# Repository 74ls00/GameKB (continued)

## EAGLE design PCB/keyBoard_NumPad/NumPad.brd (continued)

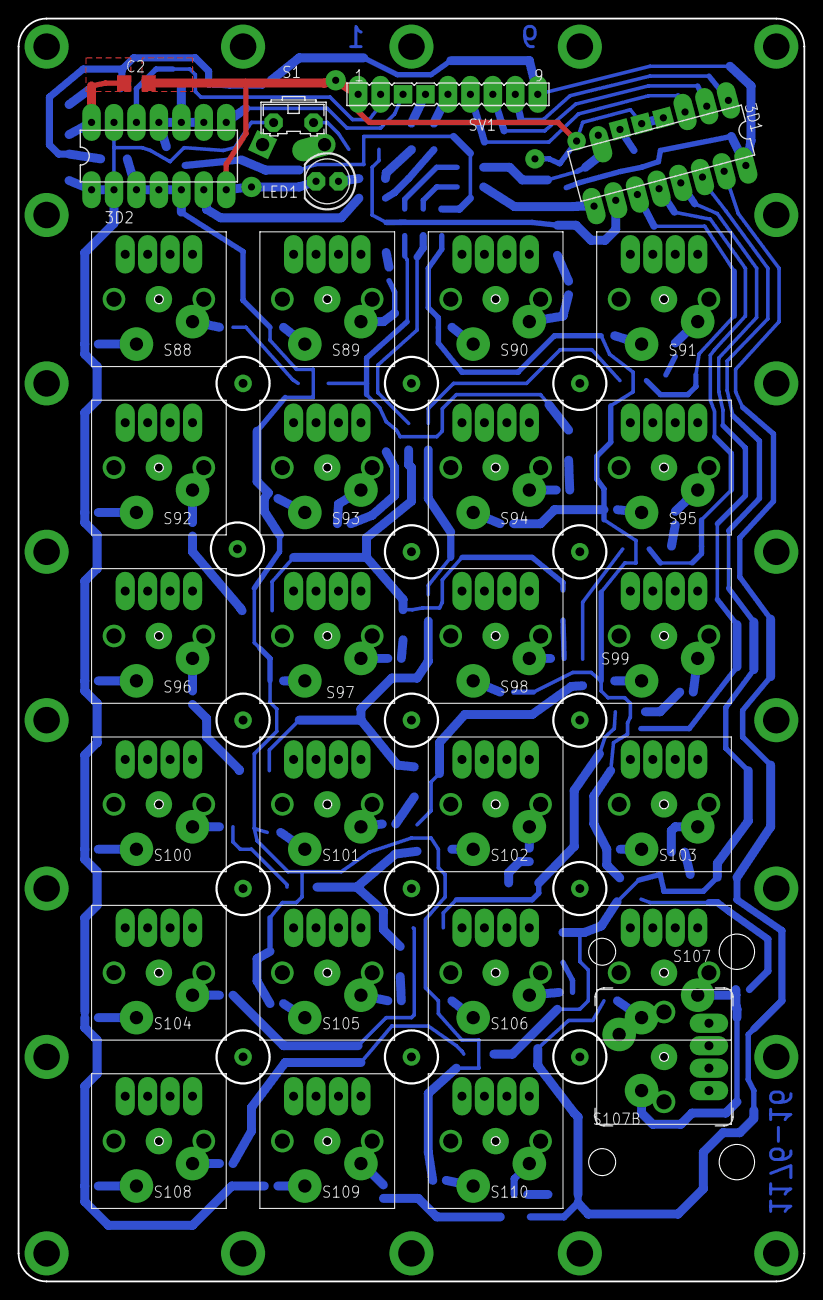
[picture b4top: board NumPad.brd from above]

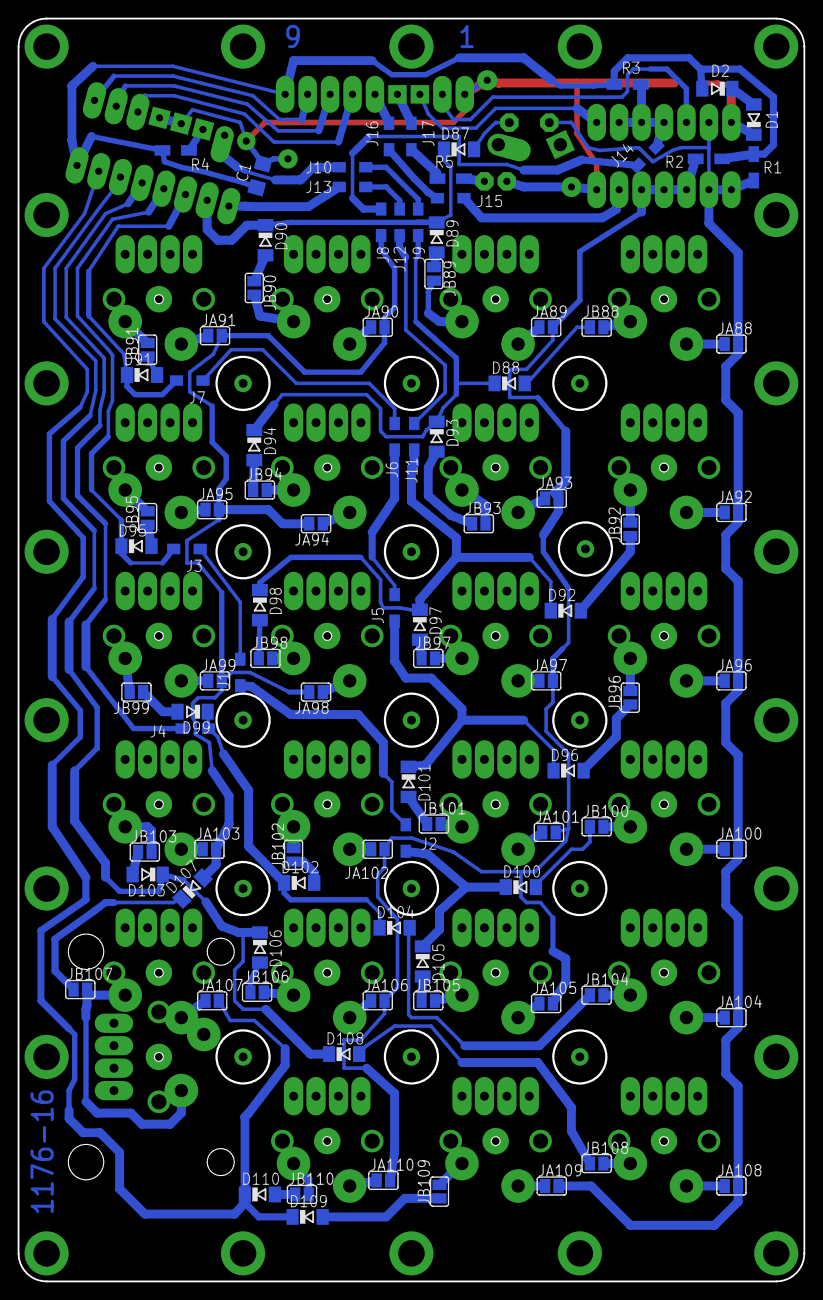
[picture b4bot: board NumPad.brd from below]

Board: 2 copper layers, 88.9 x 142.9 mm, 175 parts (23 on the bottom side), 111 nets.

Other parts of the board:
U$1, U$88, U$89, U$90, U$91, U$92, U$93, U$94, U$95, U$96, U$97, U$98, U$99, U$100, U$101, U$102, U$103, U$104, U$105, U$106, U$107, U$108, U$109, U$110: 18X18
U$2: NUMENTER
U$3, U$4, U$5, U$6, U$7, U$8, U$9, U$10, U$11, U$12, U$13, U$14, U$15, U$16, U$17, U$18, U$19, U$20, U$21, U$22, U$23, U$24: KEY
U$26: SIZE132
U$111: 37X18

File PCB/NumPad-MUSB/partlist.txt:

Partlist

Exported from NumPad.sch at 11.08.2016 8:09:16

EAGLE Version 6.3.0 Copyright (c) 1988-2012 CadSoft

Assembly variant: 

Part     Value          Device       Package      Library  Sheet

3D1      74HC138N       74HC138N     DIL16        detali   1
3D2      Ê155ÈÄ4        74HC10N      DIL14        detali   1
C1                      C-EUC1206    C1206        rcl      1
C2                      C-EUC1206    C1206        rcl      1
D1       LL4148         LL4148       SOD80C       detali   1
D2       LL4148         LL4148       SOD80C       detali   1
D87      LL4148         LL4148       SOD80C       detali   1
D88      LL4148         LL4148       SOD80C       detali   1
D89      LL4148         LL4148       SOD80C       detali   1
D90      LL4148         LL4148       SOD80C       detali   1
D91      LL4148         LL4148       SOD80C       detali   1
D92      LL4148         LL4148       SOD80C       detali   1
D93      LL4148         LL4148       SOD80C       detali   1
D94      LL4148         LL4148       SOD80C       detali   1
D95      LL4148         LL4148       SOD80C       detali   1
D96      LL4148         LL4148       SOD80C       detali   1
D97      LL4148         LL4148       SOD80C       detali   1
D98      LL4148         LL4148       SOD80C       detali   1
D99      LL4148         LL4148       SOD80C       detali   1
D100     LL4148         LL4148       SOD80C       detali   1
D101     LL4148         LL4148       SOD80C       detali   1
D102     LL4148         LL4148       SOD80C       detali   1
D103     LL4148         LL4148       SOD80C       detali   1
D104     LL4148         LL4148       SOD80C       detali   1
D105     LL4148         LL4148       SOD80C       detali   1
D106     LL4148         LL4148       SOD80C       detali   1
D107     LL4148         LL4148       SOD80C       detali   1
D108     LL4148         LL4148       SOD80C       detali   1
D109     LL4148         LL4148       SOD80C       detali   1
D110     LL4148         LL4148       SOD80C       detali   1
J1       J              J            R1206W       detali   1
J2       J              J            R1206W       detali   1
J3       J              J            R1206W       detali   1
J4       J              J            R1206W       detali   1
J5       J              J            R1206W       detali   1
J6       J              J            R1206W       detali   1
J7       J              J            R1206W       detali   1
J8       J              J            R1206W       detali   1
J9       J              J            R1206W       detali   1
J10      J              J            R1206W       detali   1
J11      J              J            R1206W       detali   1
J12      J              J            R1206W       detali   1
J13      J              J            R1206W       detali   1
J14      J              J            R1206W       detali   1
J15      J              J            R1206W       detali   1
J16      J              J            R1206W       detali   1
J17      J              J            R1206W       detali   1
JA88                    SJ           SJ           detali   1
JA89                    SJ           SJ           detali   1
JA90                    SJ           SJ           detali   1
JA91                    SJ           SJ           detali   1
JA92                    SJ           SJ           detali   1
JA93                    SJ           SJ           detali   1
JA94                    SJ           SJ           detali   1
JA95                    SJ           SJ           detali   1
JA96                    SJ           SJ           detali   1
JA97                    SJ           SJ           detali   1
JA98                    SJ           SJ           detali   1
JA99                    SJ           SJ           detali   1
JA100                   SJ           SJ           detali   1
JA101                   SJ           SJ           detali   1
JA102                   SJ           SJ           detali   1
JA103                   SJ           SJ           detali   1
JA104                   SJ           SJ           detali   1
JA105                   SJ           SJ           detali   1
JA106                   SJ           SJ           detali   1
JA107                   SJ           SJ           detali   1
JA108                   SJ           SJ           detali   1
JA109                   SJ           SJ           detali   1
JA110                   SJ           SJ           detali   1
JB88                    SJ           SJ           detali   1
JB89                    SJ           SJ           detali   1
JB90                    SJ           SJ           detali   1
JB91                    SJ           SJ           detali   1
JB92                    SJ           SJ           detali   1
JB93                    SJ           SJ           detali   1
JB94                    SJ           SJ           detali   1
JB95                    SJ           SJ           detali   1
JB96                    SJ           SJ           detali   1
JB97                    SJ           SJ           detali   1
JB98                    SJ           SJ           detali   1
JB99                    SJ           SJ           detali   1
JB100                   SJ           SJ           detali   1
JB101                   SJ           SJ           detali   1
JB102                   SJ           SJ           detali   1
JB103                   SJ           SJ           detali   1
JB104                   SJ           SJ           detali   1
JB105                   SJ           SJ           detali   1
JB106                   SJ           SJ           detali   1
JB107                   SJ           SJ           detali   1
JB108                   SJ           SJ           detali   1
JB109                   SJ           SJ           detali   1
JB110                   SJ           SJ           detali   1
LED1                    LED5MM       LED5MM       detali   1
R1       10k            R-EU_R1206W  R1206W       rcl      1
R2       10k            R-EU_R1206W  R1206W       rcl      1
R3       10k            R-EU_R1206W  R1206W       rcl      1
R4                      R-EU_R1206W  R1206W       rcl      1
R5                      R-EU_R1206W  R1206W       rcl      1
S1       NumLock        31-XX        B3F-31XX     detali   1
S88      D              CHERRY-MX-4P CHERRY-MX-4P cherrymx 1
S89      E              CHERRY-MX-4P CHERRY-MX-4P cherrymx 1
S90      F              CHERRY-MX-4P CHERRY-MX-4P cherrymx 1
S91      /              CHERRY-MX-4P CHERRY-MX-4P cherrymx 1
S92      A              CHERRY-MX-4P CHERRY-MX-4P cherrymx 1
S93      B              CHERRY-MX-4P CHERRY-MX-4P cherrymx 1
S94      C              CHERRY-MX-4P CHERRY-MX-4P cherrymx 1
S95      *              CHERRY-MX-4P CHERRY-MX-4P cherrymx 1
S96      7              CHERRY-MX-4P CHERRY-MX-4P cherrymx 1
S97      8              CHERRY-MX-4P CHERRY-MX-4P cherrymx 1
S98      9              CHERRY-MX-4P CHERRY-MX-4P cherrymx 1
S99      -              CHERRY-MX-4P CHERRY-MX-4P cherrymx 1
S100     4              CHERRY-MX-4P CHERRY-MX-4P cherrymx 1
S101     5              CHERRY-MX-4P CHERRY-MX-4P cherrymx 1
S102     6              CHERRY-MX-4P CHERRY-MX-4P cherrymx 1
S103     +              CHERRY-MX-4P CHERRY-MX-4P cherrymx 1
S104     1              CHERRY-MX-4P CHERRY-MX-4P cherrymx 1
S105     2              CHERRY-MX-4P CHERRY-MX-4P cherrymx 1
S106     3              CHERRY-MX-4P CHERRY-MX-4P cherrymx 1
S107     NumEnter       CHERRY-MX-4P CHERRY-MX-4P cherrymx 1
S107B    NumEnter       CHERRY-MX-4P CHERRY-MX-4P cherrymx 1
S108     0              CHERRY-MX-4P CHERRY-MX-4P cherrymx 1
S109     00             CHERRY-MX-4P CHERRY-MX-4P cherrymx 1
S110     .              CHERRY-MX-4P CHERRY-MX-4P cherrymx 1
SV1                     FE09-1       FE09         detali   1

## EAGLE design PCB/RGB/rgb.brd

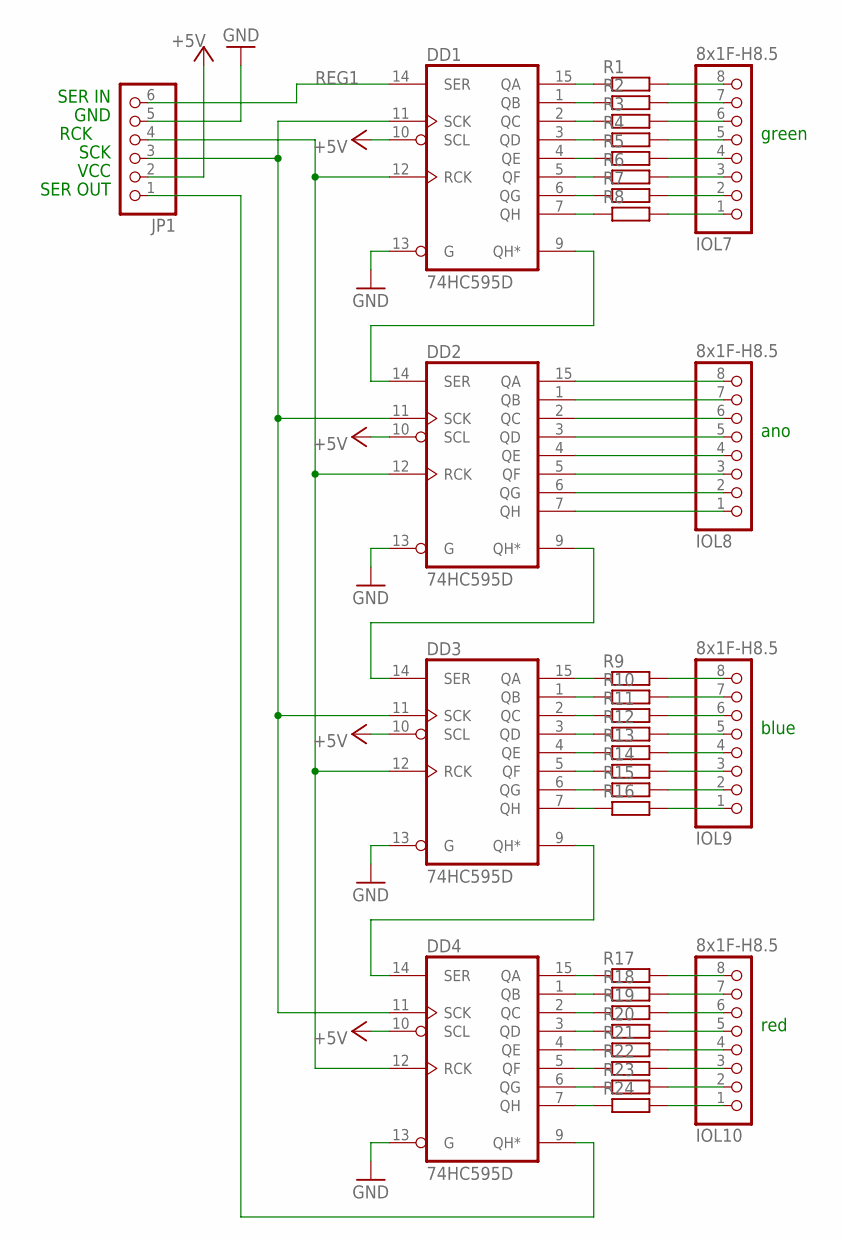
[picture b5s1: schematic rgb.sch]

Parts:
DD1, DD2, DD3, DD4: 74HC595D; SO16
IOL7, IOL8, IOL9, IOL10: 8x1F-H8.5; 1X08
JP1: PINHD-1X6; 1X06
R1, R2, R3, R4, R5, R6, R7, R8, R9, R10, R11, R12, R13, R14, R15, R16, R17, R18, R19, R20, R21, R22, R23, R24: R-EU_R0805; R0805

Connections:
+5V: DD1.10 (SCL), DD2.10 (SCL), DD3.10 (SCL), DD4.10 (SCL), JP1.2
GND: DD1.8 (GND), DD1.13 (G), DD2.8 (GND), DD2.13 (G), DD3.8 (GND), DD3.13 (G), DD4.8 (GND), DD4.13 (G), JP1.5
unnamed: DD1.15 (QA), R1.1
unnamed: DD1.1 (QB), R2.1
unnamed: DD1.2 (QC), R3.1
unnamed: DD1.3 (QD), R4.1
unnamed: DD1.4 (QE), R5.1
unnamed: DD1.5 (QF), R6.1
unnamed: DD1.6 (QG), R7.1
unnamed: DD1.7 (QH), R8.1
unnamed: DD3.15 (QA), R9.1
unnamed: DD3.1 (QB), R10.1
unnamed: DD3.2 (QC), R11.1
unnamed: DD3.3 (QD), R12.1
unnamed: DD3.4 (QE), R13.1
unnamed: DD3.5 (QF), R14.1
unnamed: DD3.6 (QG), R15.1
unnamed: DD3.7 (QH), R16.1
unnamed: DD4.15 (QA), R17.1
unnamed: DD4.1 (QB), R18.1
unnamed: DD4.2 (QC), R19.1
unnamed: DD4.3 (QD), R20.1
unnamed: DD4.4 (QE), R21.1
unnamed: DD4.5 (QF), R22.1
unnamed: DD4.6 (QG), R23.1
unnamed: DD4.7 (QH), R24.1
unnamed: IOL7.8, R1.2
unnamed: IOL7.7, R2.2
unnamed: DD2.15 (QA), IOL8.8
unnamed: DD2.1 (QB), IOL8.7
unnamed: DD2.2 (QC), IOL8.6
unnamed: DD1.9 (QH*), DD2.14 (SER)
unnamed: DD2.3 (QD), IOL8.5
unnamed: DD2.4 (QE), IOL8.4
unnamed: DD2.5 (QF), IOL8.3
unnamed: DD2.6 (QG), IOL8.2
unnamed: DD2.7 (QH), IOL8.1
unnamed: IOL7.6, R3.2
unnamed: IOL7.5, R4.2
unnamed: IOL7.4, R5.2
unnamed: IOL7.3, R6.2
unnamed: IOL7.2, R7.2
unnamed: IOL7.1, R8.2
unnamed: IOL9.8, R9.2
unnamed: IOL9.7, R10.2
unnamed: IOL9.6, R11.2
unnamed: IOL9.5, R12.2
unnamed: IOL9.4, R13.2
unnamed: IOL9.3, R14.2
unnamed: IOL9.2, R15.2
unnamed: IOL9.1, R16.2
unnamed: IOL10.8, R17.2
unnamed: IOL10.7, R18.2
unnamed: IOL10.6, R19.2
unnamed: IOL10.5, R20.2
unnamed: IOL10.4, R21.2
unnamed: IOL10.3, R22.2
unnamed: IOL10.2, R23.2
unnamed: IOL10.1, R24.2
unnamed: DD4.9 (QH*), JP1.1
unnamed: DD1.11 (SCK), DD2.11 (SCK), DD3.11 (SCK), DD4.11 (SCK), JP1.3
unnamed: DD1.12 (RCK), DD2.12 (RCK), DD3.12 (RCK), DD4.12 (RCK), JP1.4
unnamed: DD2.9 (QH*), DD3.14 (SER)
unnamed: DD3.9 (QH*), DD4.14 (SER)
REG1: DD1.14 (SER), JP1.6
VCC: DD1.16 (VCC), DD2.16 (VCC), DD3.16 (VCC), DD4.16 (VCC)

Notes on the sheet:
green
ano
blue
red
SER IN
SER OUT
GND
VCC
SCK
RCK

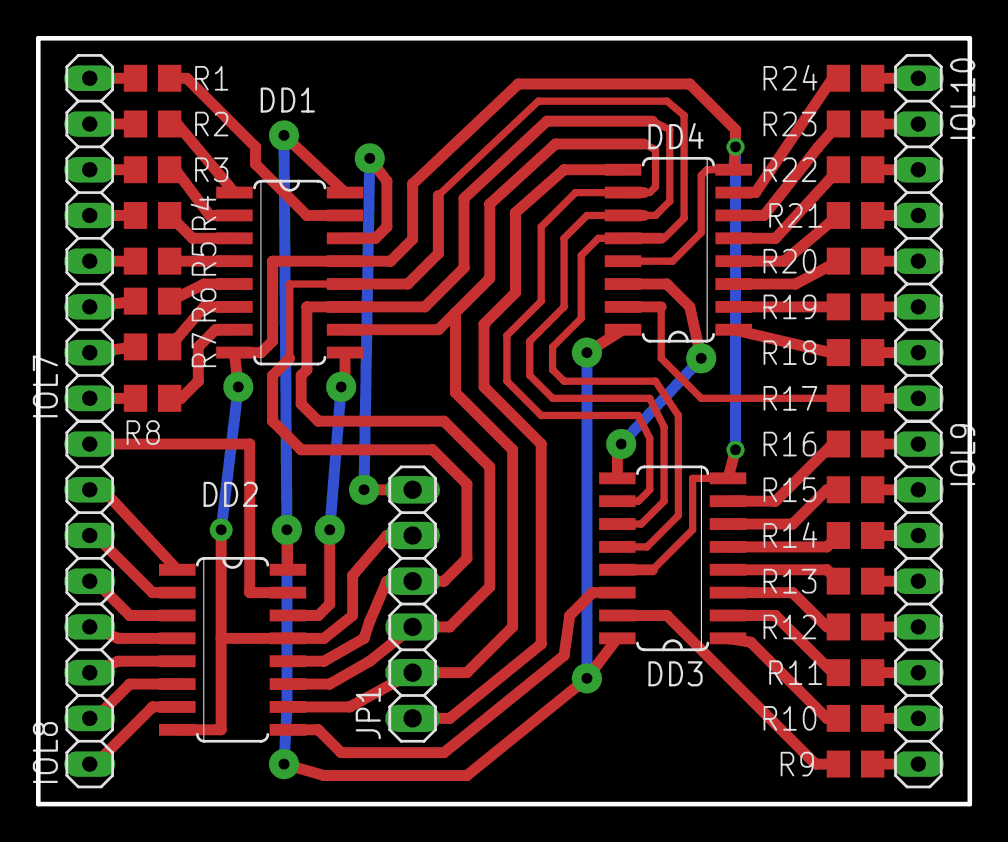
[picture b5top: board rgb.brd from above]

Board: 2 copper layers, 51.8 x 42.5 mm, 33 parts (0 on the bottom side), 66 nets.

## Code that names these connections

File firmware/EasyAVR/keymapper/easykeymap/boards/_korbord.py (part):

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#  |   avr           |      out_logic
#  |    |  port_avr  |         |   port_fw
#  |    |    |       |         |      |
# A0 = 36 = PD2 - 3,4,5   != 3D2_6  = 16 kbn3
# A1 = 37 = PD3 - 9,10,11 != 3D2_8  = 15 kbn2
# A2 = 38 = PD1 - 1,2,13  != 3D2_12 = 14 kbn1
# A4   40                             12 kbb1 
# D6   27                             10 kbb2
# D5   31   PC6                        1 kbb3
# D4   25   PD4                        7 kbb4    (x,7)
# A5   41                             11 kbb5
# D2   19   PD1                        4 kbb6
# D3(18) D7(1)  ? не нашёлся                                    
#
# D3    18  PD0                        3 kba2
# D0    20  PD2                        5 kba3
# D1    21  PD3                        6 kba4
# TxLED 22  PD5                        8 kba5
# D12   26  PD6                        9 kba6
# A3    39  PF4                       13 kba1

# keyBoard A (PCB_A) 
# порт в коде               0      4      2      6      1      5     3     7
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
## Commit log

2016-07-22 add led.c
2016-07-23 pcb np
2016-07-23 num src
2016-07-24 edit map
2016-07-28 16-07-28
2016-07-28 1087pin img
2016-07-29 + stab reserv
2016-07-29 f np1
2016-07-30 cherry datasheet
2016-07-31 move
2016-08-01 move 3
2016-08-03 fix rm
2016-08-03 eavr
2016-08-04 tmk clear
2016-08-04 bad e
2016-08-04 fix ek
2016-08-04 move 2 fw
2016-08-04 add rm
2016-08-04 add rm pic
2016-08-05 add eavr fw
2016-08-05 add ry caps
2016-08-05 del 1 wire
2016-08-06 move +m2
2016-08-06 del f
2016-08-07 arc1
2016-08-15 get all vil
2016-08-16 fix b
2016-08-17 pcb b
2016-08-17 add kesize table. bad pcb a b
2016-08-18 new pcb >
2016-08-18 pcb b > ab
2016-08-18 pcb b > ab .2
2016-08-18 pcb new b ab
2016-08-18 pcb b ok
2016-08-18 b pl mod
2016-08-19 new pcb b
2016-08-19 del old
2016-08-19 contr
2016-08-20 cont fe11s
2016-08-21 pcb b mov det
2016-08-22 b d1 d1 sw
2016-08-22 fw 3l
2016-08-22 fw 4l
2016-08-22 fw b ok
2016-08-22 rus fix
2016-08-22 sh c
2016-08-23 fw add
2016-08-23 pcb c
2016-08-24 new pcb a >
2016-08-24 pcb b old. pcb a ver txt
2016-08-24 stab
2016-08-26 test
2016-08-26 test 2
2016-08-26 test 3
2016-08-26 test 4
2016-08-26 pcb a n>
2016-08-26 pcb a 2
2016-08-26 pcb a 3
2016-08-26 pcb a 4
2016-08-27 pcb c new progr >
2016-08-27 - leo dir
2016-08-27 sw ls
2016-08-27 sw s10
2016-08-27 pcb a r
2016-08-28 pcb a
2016-08-28 pcb a +
2016-09-02 kb lay ab
2016-09-04 vil_23
2016-09-04 vil_24
2016-09-05 vil_25
2016-09-05 vil_26
2016-09-05 vil_27
2016-09-07 vil_28
2016-09-07 vil_29
2016-09-07 vil_30
2016-09-07 vil_31
2016-09-08 vil_32
2016-09-08 vil_33
2016-09-08 vil_34
2016-09-15 vil_35
2016-09-18 vil_36 new log on
2016-09-18 vil_37
2016-09-18 vil_38
2016-09-18 vil_39
2016-09-18 vil_40
2016-09-19 vil_41
2016-09-20 vil_42
2016-09-20 vil_43
2016-09-20 vil_44
2016-09-20 vil_45
2016-09-21 vil_46
2016-09-21 vil_47
2016-09-21 vil_48
2016-09-21 vil_49
2016-09-23 vil_50
2016-09-29 pcb abn ok
2016-09-30 del _korbord_ab.py
2016-09-30 del m
2016-10-01 fw 0.2
2016-10-05 fw 0.3
2016-10-25 копейки
2017-01-10 add python portable
2017-01-10 add libusb0
2017-01-14 del tmk
2017-01-16 del egg
2017-01-18 add tb test
2017-01-19 +prog
2017-01-19 fw mov
2018-08-05 add stab pcb a
2018-08-07 add1
2018-08-07 add2
2018-08-07 add22
2018-08-07 add b
2018-08-13 kb swap
